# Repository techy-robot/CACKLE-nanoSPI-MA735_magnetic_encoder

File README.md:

---
modified: 2025-11-07T22:07:46-07:00
---

# nanoSPI MA735 magnetic encoder

> [!TIP]
> This board is part of a larger modular control board ecosystem, [CACKLE](https://github.com/techy-robot/CACKLE)

This is a super compact SPI magnetic encoder, with the flex cable being 2.4mm wide and 100mm long, and the tip around 5.6mm diameter. It is quite simple, and supports on shaft or side-shaft mounting with correction.

It supports a max of 25mhz bus speed, though practically speaking this is closer to 20mhz. It supports SPI mode 0 or 3, detecting automatically.

The sensor itself, MagAlpha MA735, has some quirks to it. It is variable resolution ranging from 9 to 13 bit which is inversely proportional to its speed. If you want the max measurement speed at 60k rpm, then you will have to read 9-bit angles. This is all dictated by the Filter Window setting, resolution and speed are derived from this setting.

This can be used as a template for other nanoSPI sensors, or cables.

Also, the connectors for these sensors with a 0.35mm pitch are SUPER finicky to actually solder by hand, reflow is 1000% recommended. You will burn the plastic onto a soldering iron in one swipe.

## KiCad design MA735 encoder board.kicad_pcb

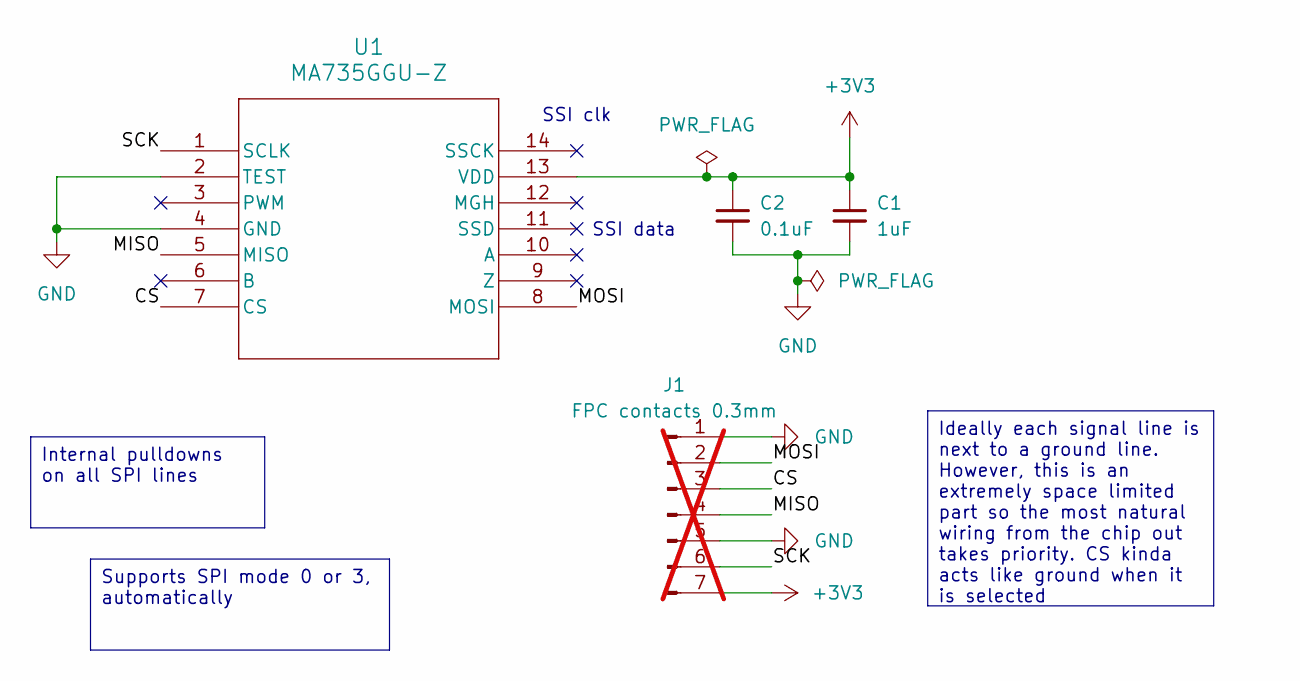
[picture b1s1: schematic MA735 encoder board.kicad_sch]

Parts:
C1: 1uF; C_0402_1005Metric; LCSC C52923
C2: 0.1uF; C_0402_1005Metric; LCSC C1525
J1: FPC contacts 0.3mm; 7pin_fpc_contact_0.3mmptich; not fitted
U1: MA735GGU-Z; UTQFN-14_MA735_MNP; LCSC C17233427

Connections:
+3V3: C1.1, C2.1, J1.7, U1.13 (VDD)
/CS: J1.3, U1.7 (CS)
/MISO: J1.4, U1.5 (MISO)
/MOSI: J1.2, U1.8 (MOSI)
/SCK: J1.6, U1.1 (SCLK)
GND: C1.2, C2.2, J1.1, J1.5, U1.2 (TEST), U1.4 (GND)

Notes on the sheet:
SSI clk
SSI data
Supports SPI mode 0 or 3, automatically
Ideally each signal line is next to a ground line. However, this is an extremely space limited part so the most natural wiring from the chip out takes priority. CS kinda acts like ground when it is selected
Internal pulldowns on all SPI lines

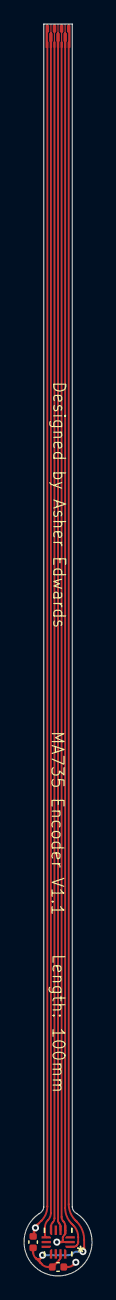
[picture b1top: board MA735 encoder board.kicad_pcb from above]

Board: 2 copper layers, 5.7 x 105.5 mm, 4 parts (0 on the bottom side), 6 nets.

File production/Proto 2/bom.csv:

Designator,Footprint,Quantity,Value,LCSC Part #
C1,0402,1,1uF,C52923
C2,0402,1,0.1uF,C1525
J1,7pin_fpc_contact_0.3mmptich,1,FPC contacts 0.3mm,
U1,UTQFN-14_MA735_MNP,1,MA735GGU-Z,C17233427

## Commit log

2024-12-31 Added MA735 encoder nanoSPI device
    This is a new line for what the 7 pin FPC SPI cables are.
2025-01-01 Exported Gerbers for MA735 encoder
2025-01-01 Updated files for JLC DFM checks
2025-01-02 Added schematic PDFs for all boards
2025-01-04 Added gerber zip files
2025-01-13 Added README files for each module
2025-01-13 Changed link names for schematic embeds not displayin
    In Obsidian I can see the pdf embeds perfectly fine, but Github doesn't want to show embedded PDFs. I changed the link alias to "Schematic PDF" so people know what the link is when it doesn't display
2025-03-19 Added pictures to each module
    Next I need to add readmes for each!
2025-05-06 Updated MA735 encoder
2025-05-06 Updated MA735 readme and production
2025-10-10 Moved all current production files to Proto 1.
    I haven't made a 2nd prototype yet
2025-11-07 Added License
2025-11-08 Updated README with link to main repo
2025-11-10 Added gitignore
2025-11-16 Tweaked schematic layout to be slightly less jank
2025-11-16 Added license notes
2025-11-16 Updated FPC connector to avoid clearance issues and be more consistant
2025-11-16 Added Credit on silkscreen
2025-11-16 Added stiffener behind encoder
2025-11-16 Updated graphics
2025-11-16 Added teardrops
2025-11-16 Rounded Tracks
2025-11-16 Fixed errors in DRC
2025-11-16 Added production files
2025-11-16 Updated schematic pdf
2025-11-16 Changed to Coverlay defined pads

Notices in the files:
MA735 encoder board.kicad_pcb:
Licensed under CERN-OHL-S v2
